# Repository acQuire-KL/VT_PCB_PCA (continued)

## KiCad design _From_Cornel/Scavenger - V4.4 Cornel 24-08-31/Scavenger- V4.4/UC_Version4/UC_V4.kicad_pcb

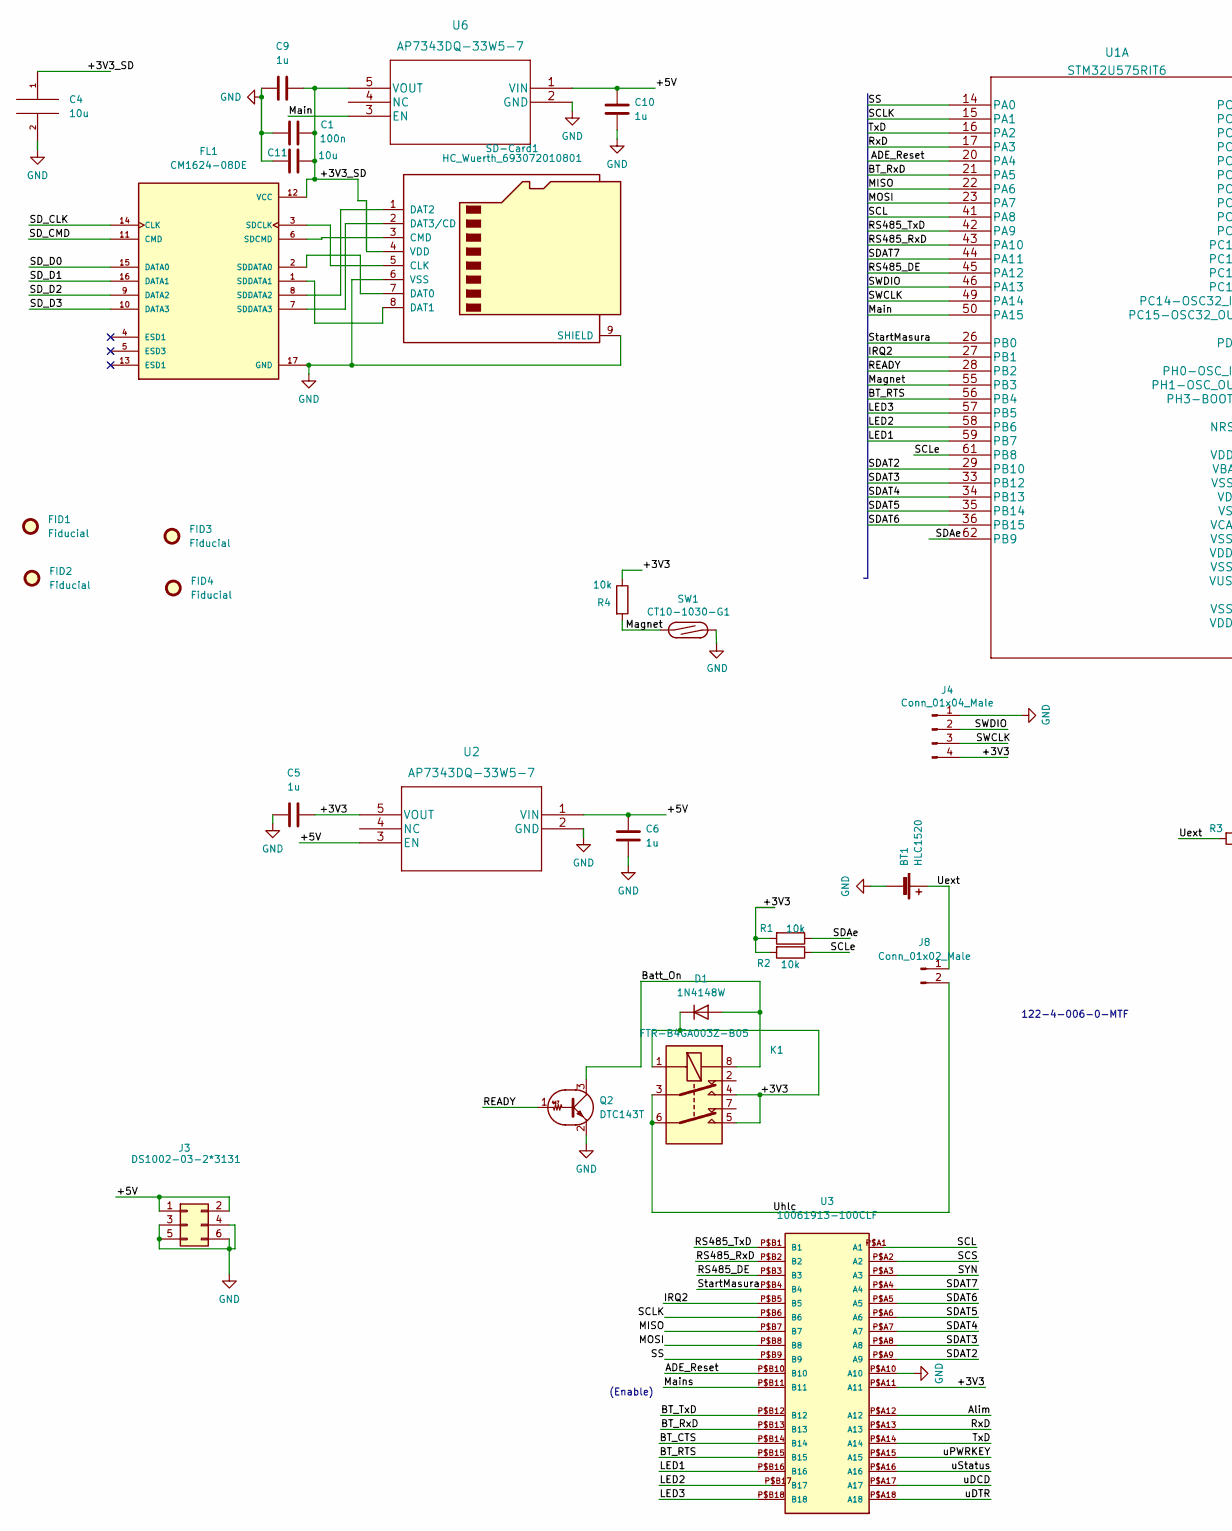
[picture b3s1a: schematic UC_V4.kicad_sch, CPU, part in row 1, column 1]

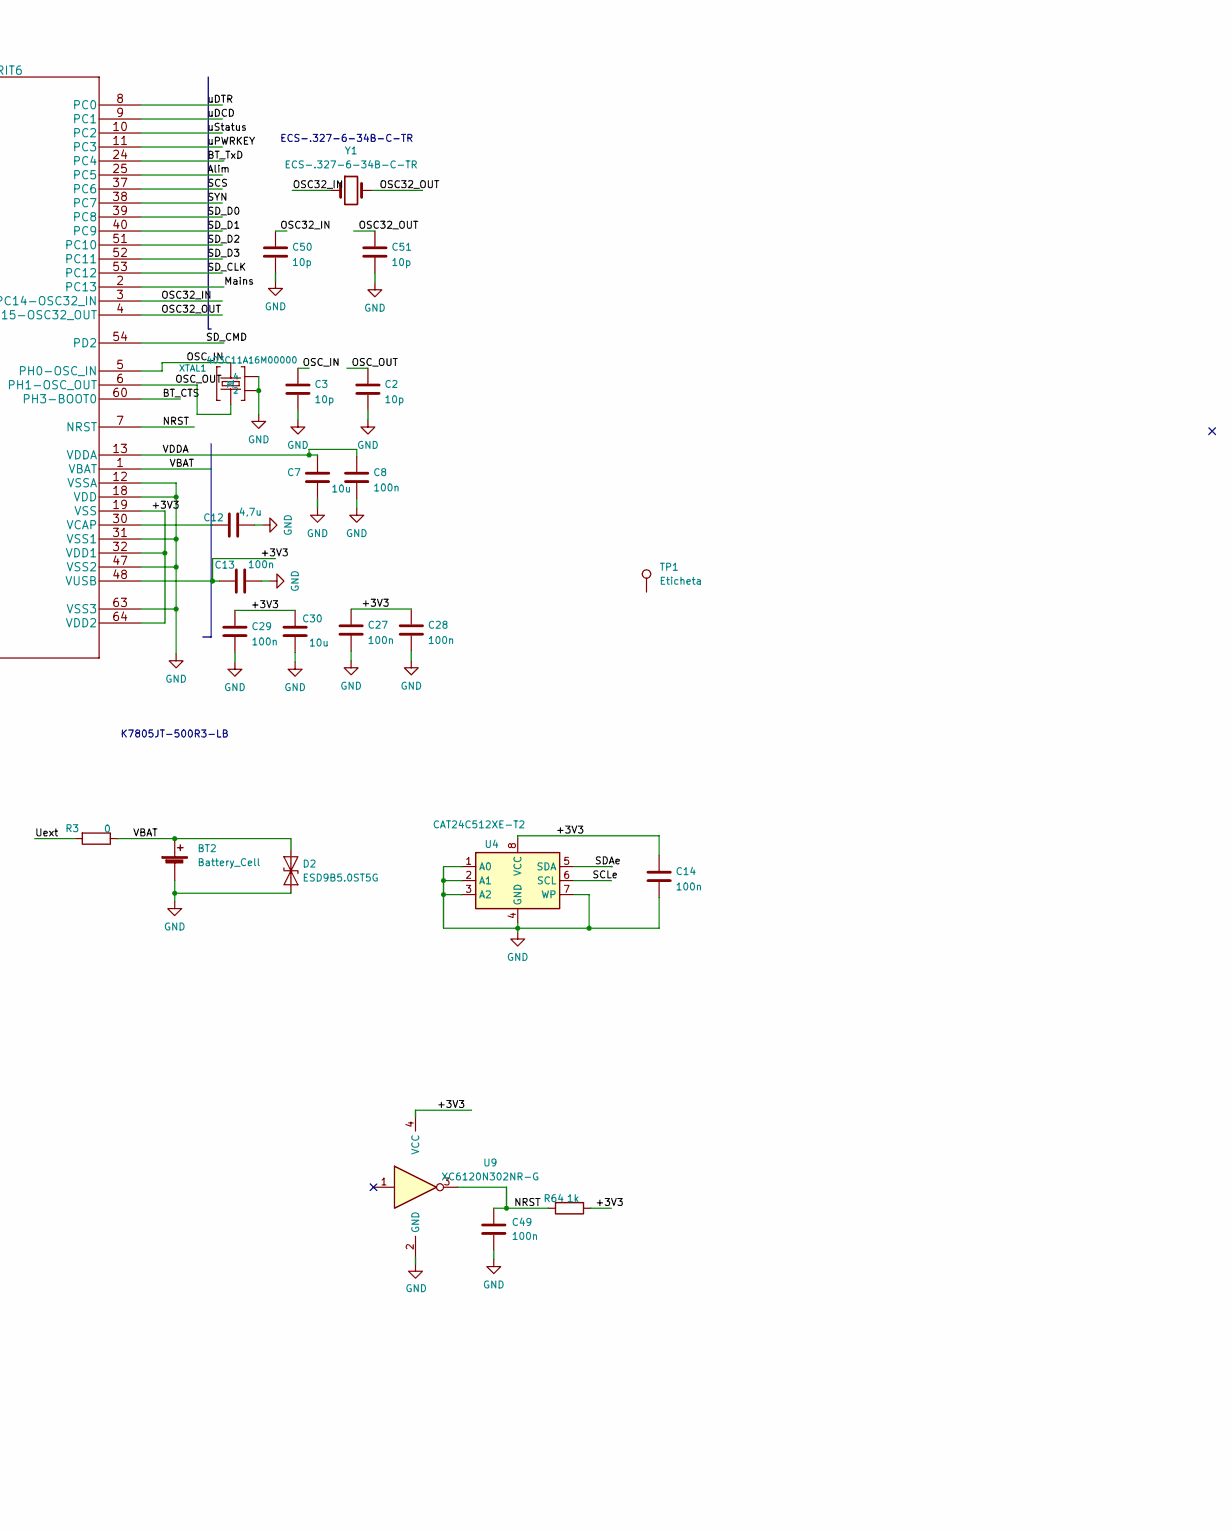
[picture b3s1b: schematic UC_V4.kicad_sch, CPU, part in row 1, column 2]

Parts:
BT1: HLC1520
BT2: Battery_Cell; BatteryHolder_Keystone_3002_1x2032
C1, C8, C13, C14, C27, C28, C29, C49: 100n; C_0603_1608Metric
C2, C3, C50, C51: 10p; C_0603_1608Metric
C4, C7, C11, C30: 10u; C_1206_3216Metric
C5, C6, C9, C10: 1u; C_0603_1608Metric
C12: 4,7u; C_1206_3216Metric
D1: 1N4148W; D_SOD-123
D2: ESD9B5.0ST5G; SOD-923_ONS
FID1, FID2, FID3, FID4: Fiducial; Fiducial_1mm_Mask2mm
FL1: CM1624-08DE; FIL_CM1624; PARTREV 4
J3: DS1002-03-2*3131; PinSocket_2x03_P2.54mm_Vertical
J4: Conn_01x04_Male; PinHeader_1x04_P2.54mm_Vertical
J8: Conn_01x02_Male; PinHeader_1x02_P2.54mm_Vertical
K1: FTR-B4GA003Z-B05; Relay_Fujitsu_FTR-B4GA003
Q2: DTC143T; SOT-23
R1, R2, R4: 10k; R_0603_1608Metric
R3: 0; R_0603_1608Metric
R64: 1k; R_0603_1608Metric
SD-Card1: HC_Wuerth_693072010801; microSD_HC_Wuerth_693072010801
SW1: CT10-1030-G1; SW_SPST_REED_CT10-XXXX-G1
TP1: Eticheta
U1: STM32U575RIT6; LQFP-64_10x10mm_P0.5mm
U2, U6: AP7343DQ-33W5-7; AP3012KTR-G1
U3: 10061913-100CLF; MPN 10061913-100CLF
U4: CAT24C512XE-T2; SO-8_3.9x4.9mm_P1.27mm
U9: XC6120N302NR-G; SC-82AA
XTAL1: 403C11A16M00000; Crystal_SMD_SeikoEpson_TSX3225-4Pin_3.2x2.5mm
Y1: ECS-.327-6-34B-C-TR; Crystal_SMD_EuroQuartz_EQ161-2Pin_3.2x1.5mm

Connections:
/+3V3: C5.2, C13.1, C14.1, C27.1, C28.1, C29.1, C30.1, D1.1 (K), J4.4, K1.1, K1.4, K1.5, R1.2, R2.2, R4.1, R64.1, U1.19 (VSS), U1.32 (VDD1), U1.48 (VUSB), U1.64 (VDD2), U2.5 (VOUT), U3.P$A11 (A11), U4.8 (VCC), U9.4 (VCC)
/+3V3_SD: C1.2, C4.1, C9.2, C11.2, FL1.12 (VCC), SD-Card1.4 (VDD), U6.5 (VOUT)
/+5V: C6.1, C10.1, J3.1, J3.2, U2.1 (VIN), U2.3 (EN), U6.1 (VIN)
/ADE_Reset: U1.20 (PA4), U3.P$B10 (B10)
/Alim: U1.25 (PC5), U3.P$A12 (A12)
/BT_CTS: U1.60 (PH3-BOOT0), U3.P$B14 (B14)
/BT_RTS: U1.56 (PB4), U3.P$B15 (B15)
/BT_RxD: U1.21 (PA5), U3.P$B13 (B13)
/BT_TxD: U1.24 (PC4), U3.P$B12 (B12)
/Batt_On: D1.2 (A), K1.8, Q2.3 (C)
/IRQ2: U1.27 (PB1), U3.P$B5 (B5)
/LED1: U1.59 (PB7), U3.P$B16 (B16)
/LED2: U1.58 (PB6), U3.P$B17 (B17)
/LED3: U1.57 (PB5), U3.P$B18 (B18)
/MISO: U1.22 (PA6), U3.P$B7 (B7)
/MOSI: U1.23 (PA7), U3.P$B8 (B8)
/Magnet: R4.2, SW1.1, U1.55 (PB3)
/Main: U1.50 (PA15), U6.3 (EN)
/Mains: U1.2 (PC13), U3.P$B11 (B11)
/NRST: C49.1, R64.2, U1.7 (NRST), U9.3
/OSC32_IN: C50.1, U1.3 (PC14-OSC32_IN), Y1.1
/OSC32_OUT: C51.1, U1.4 (PC15-OSC32_OUT), Y1.2
/OSC_IN: C3.1, U1.5 (PH0-OSC_IN), XTAL1.3
/OSC_OUT: C2.1, U1.6 (PH1-OSC_OUT), XTAL1.1
/READY: Q2.1 (B), U1.28 (PB2)
/RS485_DE: U1.45 (PA12), U3.P$B3 (B3)
/RS485_RxD: U1.43 (PA10), U3.P$B2 (B2)
/RS485_TxD: U1.42 (PA9), U3.P$B1 (B1)
/RxD: U1.17 (PA3), U3.P$A13 (A13)
/SCL: U1.41 (PA8), U3.P$A1 (A1)
/SCLK: U1.15 (PA1), U3.P$B6 (B6)
/SCLe: R2.1, U1.61 (PB8), U4.6 (SCL)
/SCS: U1.37 (PC6), U3.P$A2 (A2)
/SDAT2: U1.29 (PB10), U3.P$A9 (A9)
/SDAT3: U1.33 (PB12), U3.P$A8 (A8)
/SDAT4: U1.34 (PB13), U3.P$A7 (A7)
/SDAT5: U1.35 (PB14), U3.P$A6 (A6)
/SDAT6: U1.36 (PB15), U3.P$A5 (A5)
/SDAT7: U1.44 (PA11), U3.P$A4 (A4)
/SDAe: R1.1, U1.62 (PB9), U4.5 (SDA)
/SD_CLK: FL1.14 (CLK), U1.53 (PC12)
/SD_CMD: FL1.11 (CMD), U1.54 (PD2)
/SD_D0: FL1.15 (DATA0), U1.39 (PC8)
/SD_D1: FL1.16 (DATA1), U1.40 (PC9)
/SD_D2: FL1.9 (DATA2), U1.51 (PC10)
/SD_D3: FL1.10 (DATA3), U1.52 (PC11)
/SS: U1.14 (PA0), U3.P$B9 (B9)
/SWCLK: J4.3, U1.49 (PA14)
/SWDIO: J4.2, U1.46 (PA13)
/SYN: U1.38 (PC7), U3.P$A3 (A3)
/StartMasura: U1.26 (PB0), U3.P$B4 (B4)
/TxD: U1.16 (PA2), U3.P$A14 (A14)
/Uext: BT1.1 (+), J8.1, R3.2
/Uhlc: J8.2, K1.3, K1.6
/VBAT: BT2.1 (+), D2.2 (A2), R3.1, U1.1 (VBAT)
/VDDA: C7.1, C8.1, U1.13 (VDDA)
/uDCD: U1.9 (PC1), U3.P$A17 (A17)
/uDTR: U1.8 (PC0), U3.P$A18 (A18)
/uPWRKEY: U1.11 (PC3), U3.P$A15 (A15)
/uStatus: U1.10 (PC2), U3.P$A16 (A16)
GND: BT1.2 (-), BT2.2 (-), C1.1, C2.2, C3.2, C4.2, C5.1, C6.2, C7.2, C8.2, C9.1, C10.2, C11.1, C12.2, C13.2, C14.2, C27.2, C28.2, C29.2, C30.2, C49.2, C50.2, C51.2, D2.1 (A1), FL1.17 (GND), J3.3, J3.4, J3.5, J3.6, J4.1, Q2.2 (E), SD-Card1.6 (VSS), SD-Card1.9 (SHIELD), SW1.2, U1.12 (VSSA), U1.18 (VDD), U1.31 (VSS1), U1.47 (VSS2), U1.63 (VSS3), U2.2 (GND), U3.P$A10 (A10), U4.1 (A0), U4.2 (A1), U4.3 (A2), U4.4 (GND), U4.7 (WP), U6.2 (GND), U9.2 (GND), XTAL1.2, XTAL1.4
unnamed: C12.1, U1.30 (VCAP)
unnamed: FL1.1 (SDDATA1), SD-Card1.8 (DAT1)
unnamed: FL1.2 (SDDATA0), SD-Card1.7 (DAT0)
unnamed: FL1.3 (SDCLK), SD-Card1.5 (CLK)
unnamed: FL1.6 (SDCMD), SD-Card1.3 (CMD)
unnamed: FL1.7 (SDDATA3), SD-Card1.2 (DAT3/CD)
unnamed: FL1.8 (SDDATA2), SD-Card1.1 (DAT2)

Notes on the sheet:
ECS-.327-6-34B-C-TR
K7805JT-500R3-LB
(Enable)
122-4-006-0-MTF

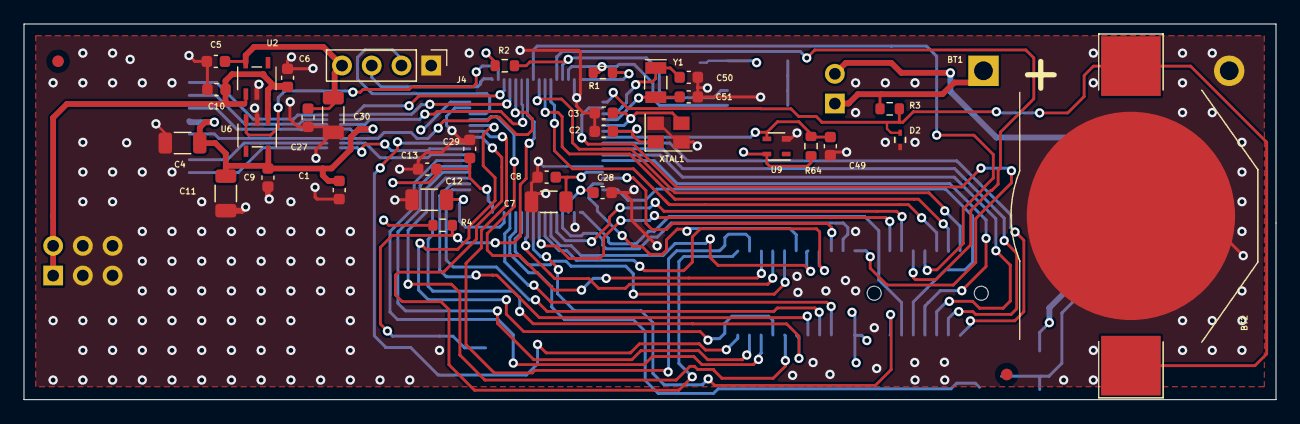
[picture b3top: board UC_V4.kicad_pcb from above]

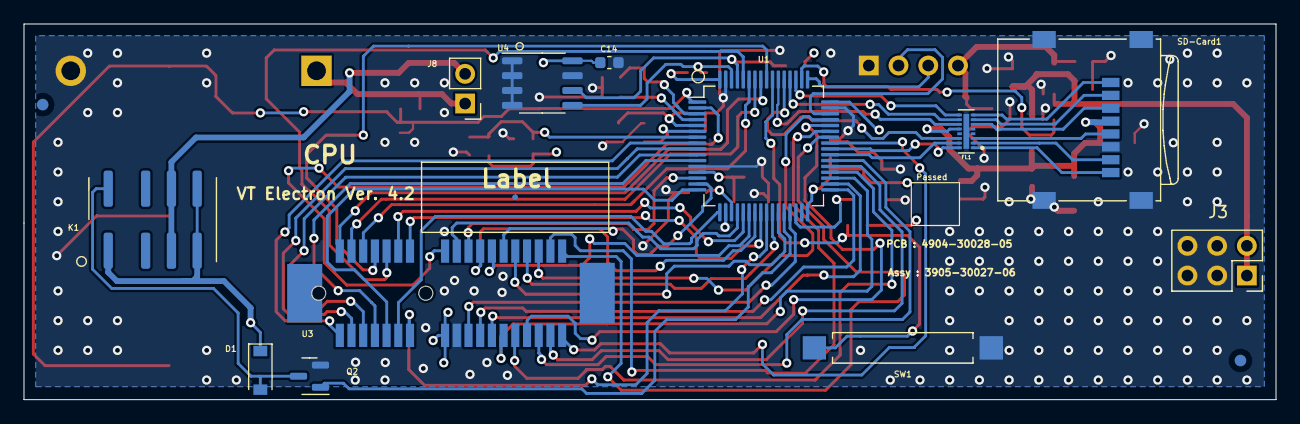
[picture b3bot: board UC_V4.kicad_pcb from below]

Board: 4 copper layers, 107.0 x 32.1 mm, 51 parts (14 on the bottom side), 68 nets.

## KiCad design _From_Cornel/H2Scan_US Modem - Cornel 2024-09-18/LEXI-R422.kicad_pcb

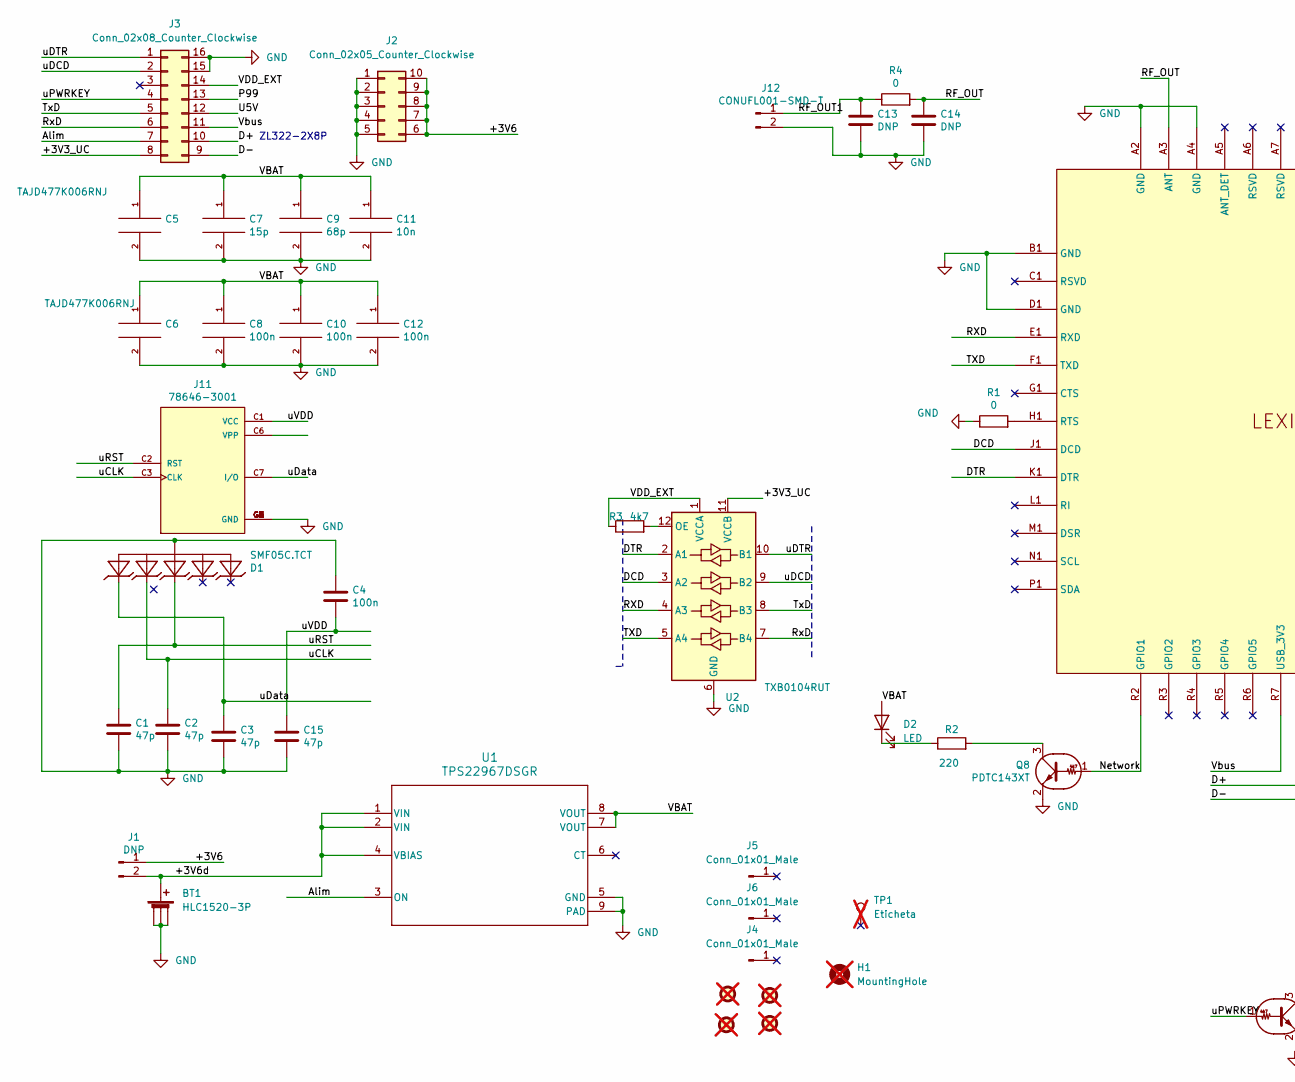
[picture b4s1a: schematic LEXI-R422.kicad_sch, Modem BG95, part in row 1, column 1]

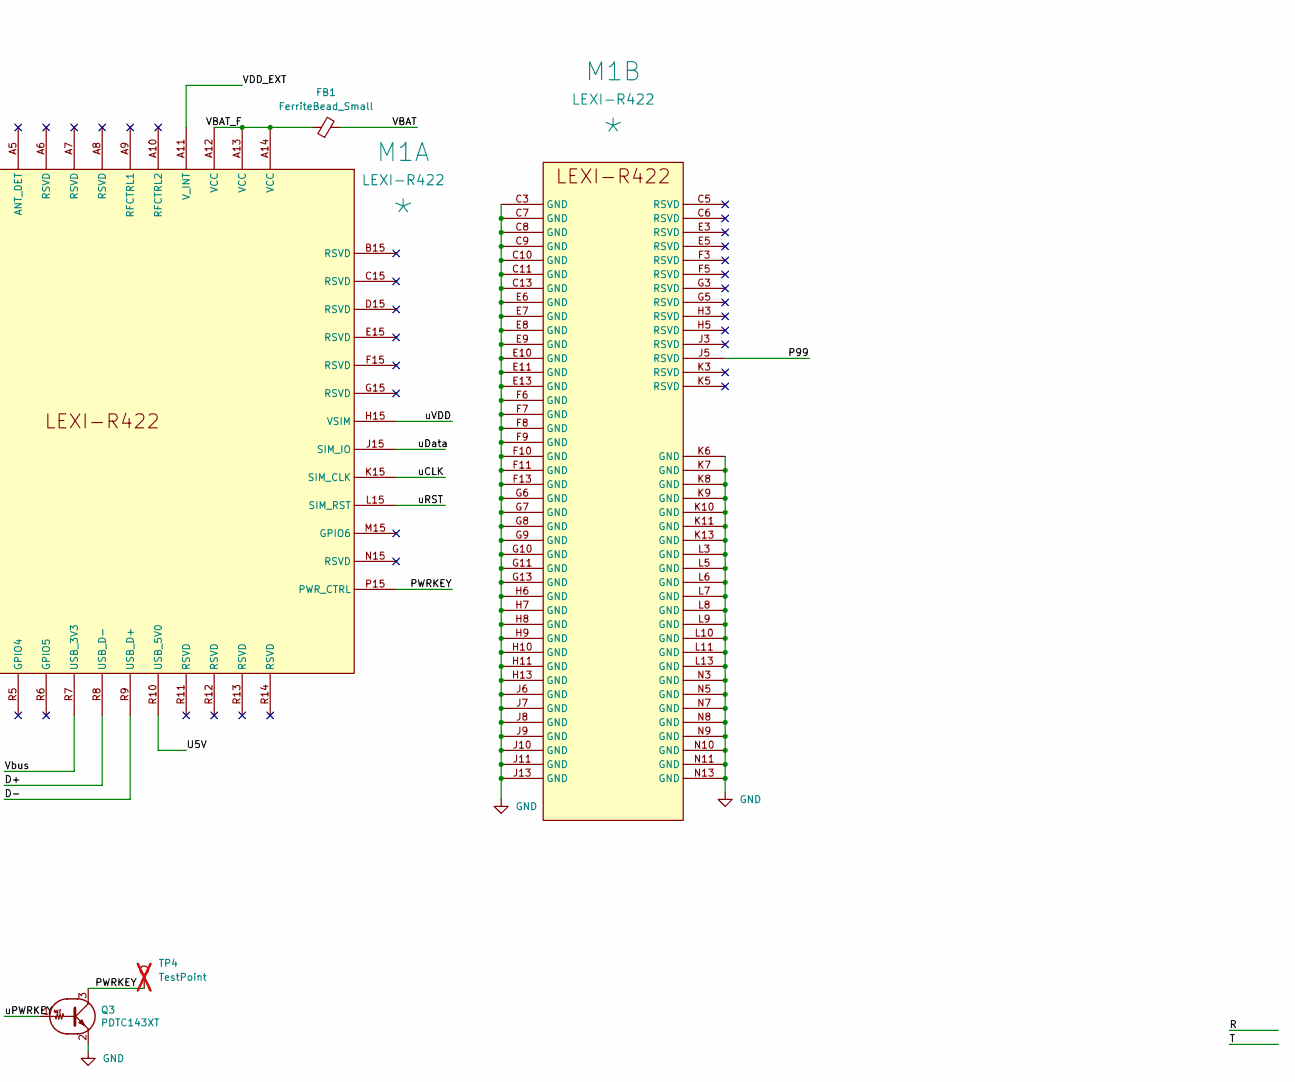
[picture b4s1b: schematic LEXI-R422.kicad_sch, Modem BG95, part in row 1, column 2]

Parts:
BT1: HLC1520-3P
C1, C2, C3, C15: 47p; C_0603_1608Metric
C4, C8, C10, C12: 100n; C_0603_1608Metric
C5, C6: TAJD477K006RNJ; CP_EIA-7361-38_AVX-V_Pad2.18x3.30mm_HandSolder
C7: 15p; C_0603_1608Metric
C9: 68p; C_0603_1608Metric
C11: 10n; C_0603_1608Metric
C13, C14: DNP; C_0603_1608Metric
D1: SMF05C.TCT; SC70-6
D2: LED; LED_0805_2012Metric
FB1: FerriteBead_Small; L_Walsin_WLFM201209x
FID1, FID2, FID3, FID4: Fiducial; Fiducial_1mm_Mask2mm; not fitted
H1: MountingHole; MountingHole_2.5mm Simpla; not fitted
J1: DNP; PinHeader_1x02_P2.54mm_Vertical_MOD
J2: Conn_02x05_Counter_Clockwise; PinHeader_2x05_P2.54mm_Vertical_SMD_MOD
J3: Conn_02x08_Counter_Clockwise; PinHeader_2x08_P2.54mm_Vertical_SMD_MOD
J4, J5, J6: Conn_01x01_Male; TestPoint_Pad_5.1x5.1mm
J11: 78646-3001; MOLEX_78646-3001; DIGI-KEY_PART_NUMBER WM9364CT-ND
J12: CONUFL001-SMD-T; U.FL_Molex_MCRF_73412-0110_Vertical
M1: LEXI-R422; LEXI; Manufacturer P/N *
Q3, Q8: PDTC143XT; SOT-23
R1, R4: 0; R_0603_1608Metric
R2: 220; R_0603_1608Metric
R3: 4k7; R_0603_1608Metric
TP1: Eticheta; not fitted
TP4: TestPoint; TestPoint_Pad_D1.5mm; not fitted
U1: TPS22967DSGR; WSON-8-1EP_2x2mm_P0.5mm_EP0.9x1.6mm_ThermalVias
U2: TXB0104RUT; Texas_R_PUQFN-N12

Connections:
/+3V3_UC: J3.8, U2.11 (VCCB)
/+3V6: J1.1, J2.6, J2.7, J2.8, J2.9, J2.10
/+3V6d: BT1.1 (+), J1.2, U1.1 (VIN), U1.2 (VIN), U1.4 (VBIAS)
/Alim: J3.7, U1.3 (ON)
/D+: J3.10, M1.R8 (USB_D-)
/D-: J3.9, M1.R9 (USB_D+)
/DCD: M1.J1 (DCD), U2.3 (A2)
/DTR: M1.K1 (DTR), U2.2 (A1)
/Network: M1.R2 (GPIO1), Q8.1 (B)
/P99: J3.13, M1.J5 (RSVD)
/PWRKEY: M1.P15 (PWR_CTRL), Q3.3 (C), TP4.1
/RF_OUT: C14.1, M1.A3 (ANT), R4.2
/RF_OUT1: C13.1, J12.1, R4.1
/RXD: M1.E1 (RXD), U2.4 (A3)
/RxD: J3.6, U2.7 (B4)
/TXD: M1.F1 (TXD), U2.5 (A4)
/TxD: J3.5, U2.8 (B3)
/U5V: J3.12, M1.R10 (USB_5V0)
/VBAT: C5.1, C6.1, C7.1, C8.1, C9.1, C10.1, C11.1, C12.1, D2.2 (A), FB1.2, U1.7 (VOUT), U1.8 (VOUT)
/VBAT_F: FB1.1, M1.A12 (VCC), M1.A13 (VCC), M1.A14 (VCC)
/VDD_EXT: J3.14, M1.A11 (V_INT), R3.1, U2.1 (VCCA)
/Vbus: J3.11, M1.R7 (USB_3V3)
/uCLK: C2.1, D1.5, J11.C3 (CLK), M1.K15 (SIM_CLK)
/uDCD: J3.2, U2.9 (B2)
/uDTR: J3.1, U2.10 (B1)
/uData: C3.1, D1.6, J11.C7 (I/O), M1.J15 (SIM_IO)
/uPWRKEY: J3.4, Q3.1 (B)
/uRST: C1.1, D1.4, J11.C2 (RST), M1.L15 (SIM_RST)
/uVDD: C4.2, C15.1, J11.C1 (VCC), M1.H15 (VSIM)
GND: BT1.2 (-), BT1.3 (-), BT1.4 (-), C1.2, C2.2, C3.2, C4.1, C5.2, C6.2, C7.2, C8.2, C9.2, C10.2, C11.2, C12.2, C13.2, C14.2, C15.2, D1.2, J2.1, J2.2, J2.3, J2.4, J2.5, J3.15, J3.16, J11.C5 (GND), J11.G1 (GND), J11.G2 (GND), J11.G3 (GND), J11.G4 (GND), J11.G5 (GND), J11.G6 (GND), J12.2, M1.A2 (GND), M1.A4 (GND), M1.B1 (GND), M1.C3 (GND), M1.C7 (GND), M1.C8 (GND), M1.C9 (GND), M1.C10 (GND), M1.C11 (GND), M1.C13 (GND), M1.D1 (GND), M1.E6 (GND), M1.E7 (GND), M1.E8 (GND), M1.E9 (GND), M1.E10 (GND), M1.E11 (GND), M1.E13 (GND), M1.F6 (GND), M1.F7 (GND), M1.F8 (GND), M1.F9 (GND), M1.F10 (GND), M1.F11 (GND), M1.F13 (GND), M1.G6 (GND), M1.G7 (GND), M1.G8 (GND), M1.G9 (GND), M1.G10 (GND), M1.G11 (GND), M1.G13 (GND), M1.H6 (GND), M1.H7 (GND), M1.H8 (GND), M1.H9 (GND), M1.H10 (GND), M1.H11 (GND), M1.H13 (GND), M1.J6 (GND), M1.J7 (GND), M1.J8 (GND), M1.J9 (GND), M1.J10 (GND), M1.J11 (GND), M1.J13 (GND), M1.K6 (GND), M1.K7 (GND), M1.K8 (GND), M1.K9 (GND), M1.K10 (GND), M1.K11 (GND), M1.K13 (GND), M1.L3 (GND), M1.L5 (GND), M1.L6 (GND), M1.L7 (GND), M1.L8 (GND), M1.L9 (GND), M1.L10 (GND), M1.L11 (GND), M1.L13 (GND), M1.N3 (GND), M1.N5 (GND), M1.N7 (GND), M1.N8 (GND), M1.N9 (GND), M1.N10 (GND), M1.N11 (GND), M1.N13 (GND), Q3.2 (E), Q8.2 (E), R1.1, U1.5 (GND), U1.9 (PAD), U2.6 (GND)
unnamed: D2.1 (K), R2.1
unnamed: M1.H1 (RTS), R1.2
unnamed: Q8.3 (C), R2.2
unnamed: R3.2, U2.12 (OE)

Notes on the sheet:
ZL322-2X8P

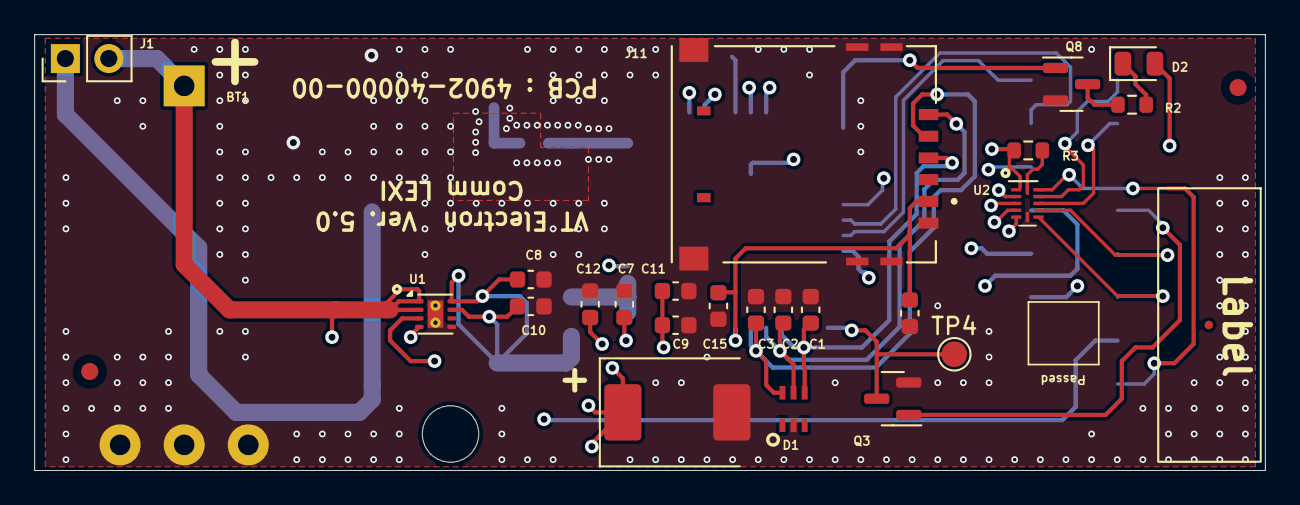
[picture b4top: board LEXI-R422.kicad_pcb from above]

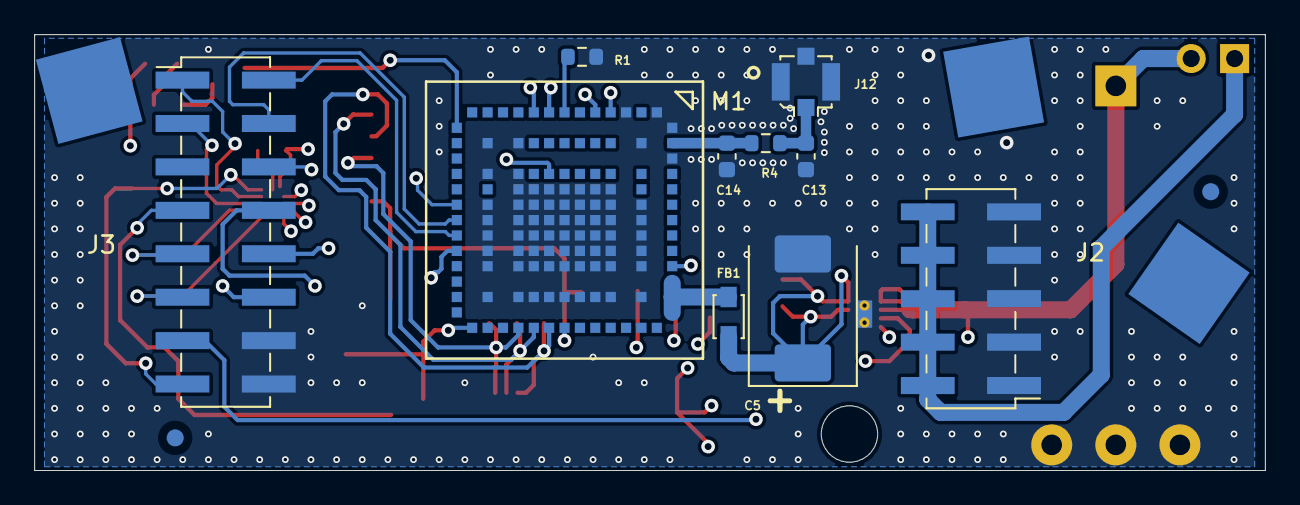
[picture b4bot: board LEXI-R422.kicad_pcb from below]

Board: 4 copper layers, 72.0 x 25.5 mm, 43 parts (15 on the bottom side), 34 nets.

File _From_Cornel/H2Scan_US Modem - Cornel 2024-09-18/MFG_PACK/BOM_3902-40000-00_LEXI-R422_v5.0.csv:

"VTPN","Reference","Value","Datasheet","Footprint","Qty","DNP"
"4200-00010-00","BT1","HLC1520-3P","~","Battery:HLC1520-3P","1",""
"4106-00080-00","C1,C2,C3,C15","47p","~","Capacitor_SMD:C_0603_1608Metric","4",""
"4106-00020-00","C4,C8,C10,C12","100n","~","Capacitor_SMD:C_0603_1608Metric","4",""
"4128-00100-00","C5,C6","TAJD477K006RNJ","~","Capacitor_Tantalum_SMD:CP_EIA-7361-38_AVX-V_Pad2.18x3.30mm_HandSolder","2",""
"4106-00070-00","C7","15p","~","Capacitor_SMD:C_0603_1608Metric","1",""
"4106-00060-00","C9","68p","~","Capacitor_SMD:C_0603_1608Metric","1",""
"4106-00015-00","C11","10n","~","Capacitor_SMD:C_0603_1608Metric","1",""
"-- mixed values --","C13,C14,J1","DNP","~","-- mixed values --","3",""
"4724-00010-00","D1","SMF05C.TCT","","Diode_SMD:SC70-6","1",""
"","FID1,FID2,FID3,FID4","Fiducial","~","Fiducial:Fiducial_1mm_Mask2mm","4","DNP"
"","H1","MountingHole","~","MountingHole:MountingHole_2.5mm  Simpla","1","DNP"
"4402-00020-00","J2","Conn_02x05_Counter_Clockwise","~","Connector_PinHeader_2.54mm:PinHeader_2x05_P2.54mm_Vertical_SMD_MOD","1",""
"4402-00030-00","J3","Conn_02x08_Counter_Clockwise","~","Connector_PinHeader_2.54mm:PinHeader_2x08_P2.54mm_Vertical_SMD_MOD","1",""
"4753-00010-00","J4,J5,J6","Conn_01x01_Male","~","TestPoint:TestPoint_Pad_5.1x5.1mm","3",""
"4414-00020-00","J11","78646-3001","","Connector_Molex:MOLEX_78646-3001","1",""
"4416-00010-00","J12","CONUFL001-SMD-T","~","Connector_Coaxial:U.FL_Molex_MCRF_73412-0110_Vertical","1",""
"4500-00010-00","Q3,Q8","PDTC143XT","","Package_TO_SOT_SMD:SOT-23","2",""
"4006-00001-00","R1,R4","0","~","Resistor_SMD:R_0603_1608Metric","2",""
"4006-00020-00","R2","220","~","Resistor_SMD:R_0603_1608Metric","1",""
"4006-00150-00","R3","4k7","~","Resistor_SMD:R_0603_1608Metric","1",""
"","TP1","Eticheta","~","Symbol:Eticheta","1","DNP"
"4702-01010-00","U1","TPS22967DSGR","TPS22967DSGR","Package_SON:WSON-8-1EP_2x2mm_P0.5mm_EP0.9x1.6mm_ThermalVias","1",""
"4702-00010-00","U2","TXB0104RUT","http://www.ti.com/lit/ds/symlink/txb0104.pdf","Package_DFN_QFN:Texas_R_PUQFN-N12","1",""
"4300-01010-00","FB1","FerriteBead_Small","~","Inductor_SMD:L_Walsin_WLFM201209x","1",""
"4752-01010-00","D2","LED","~","LED_SMD:LED_0805_2012Metric","1",""
"","TP4","TestPoint","~","TestPoint:TestPoint_Pad_D1.5mm","1","DNP"
"4716-00020-00","M1","LEXI-R422","","ublox:LEXI","1",""

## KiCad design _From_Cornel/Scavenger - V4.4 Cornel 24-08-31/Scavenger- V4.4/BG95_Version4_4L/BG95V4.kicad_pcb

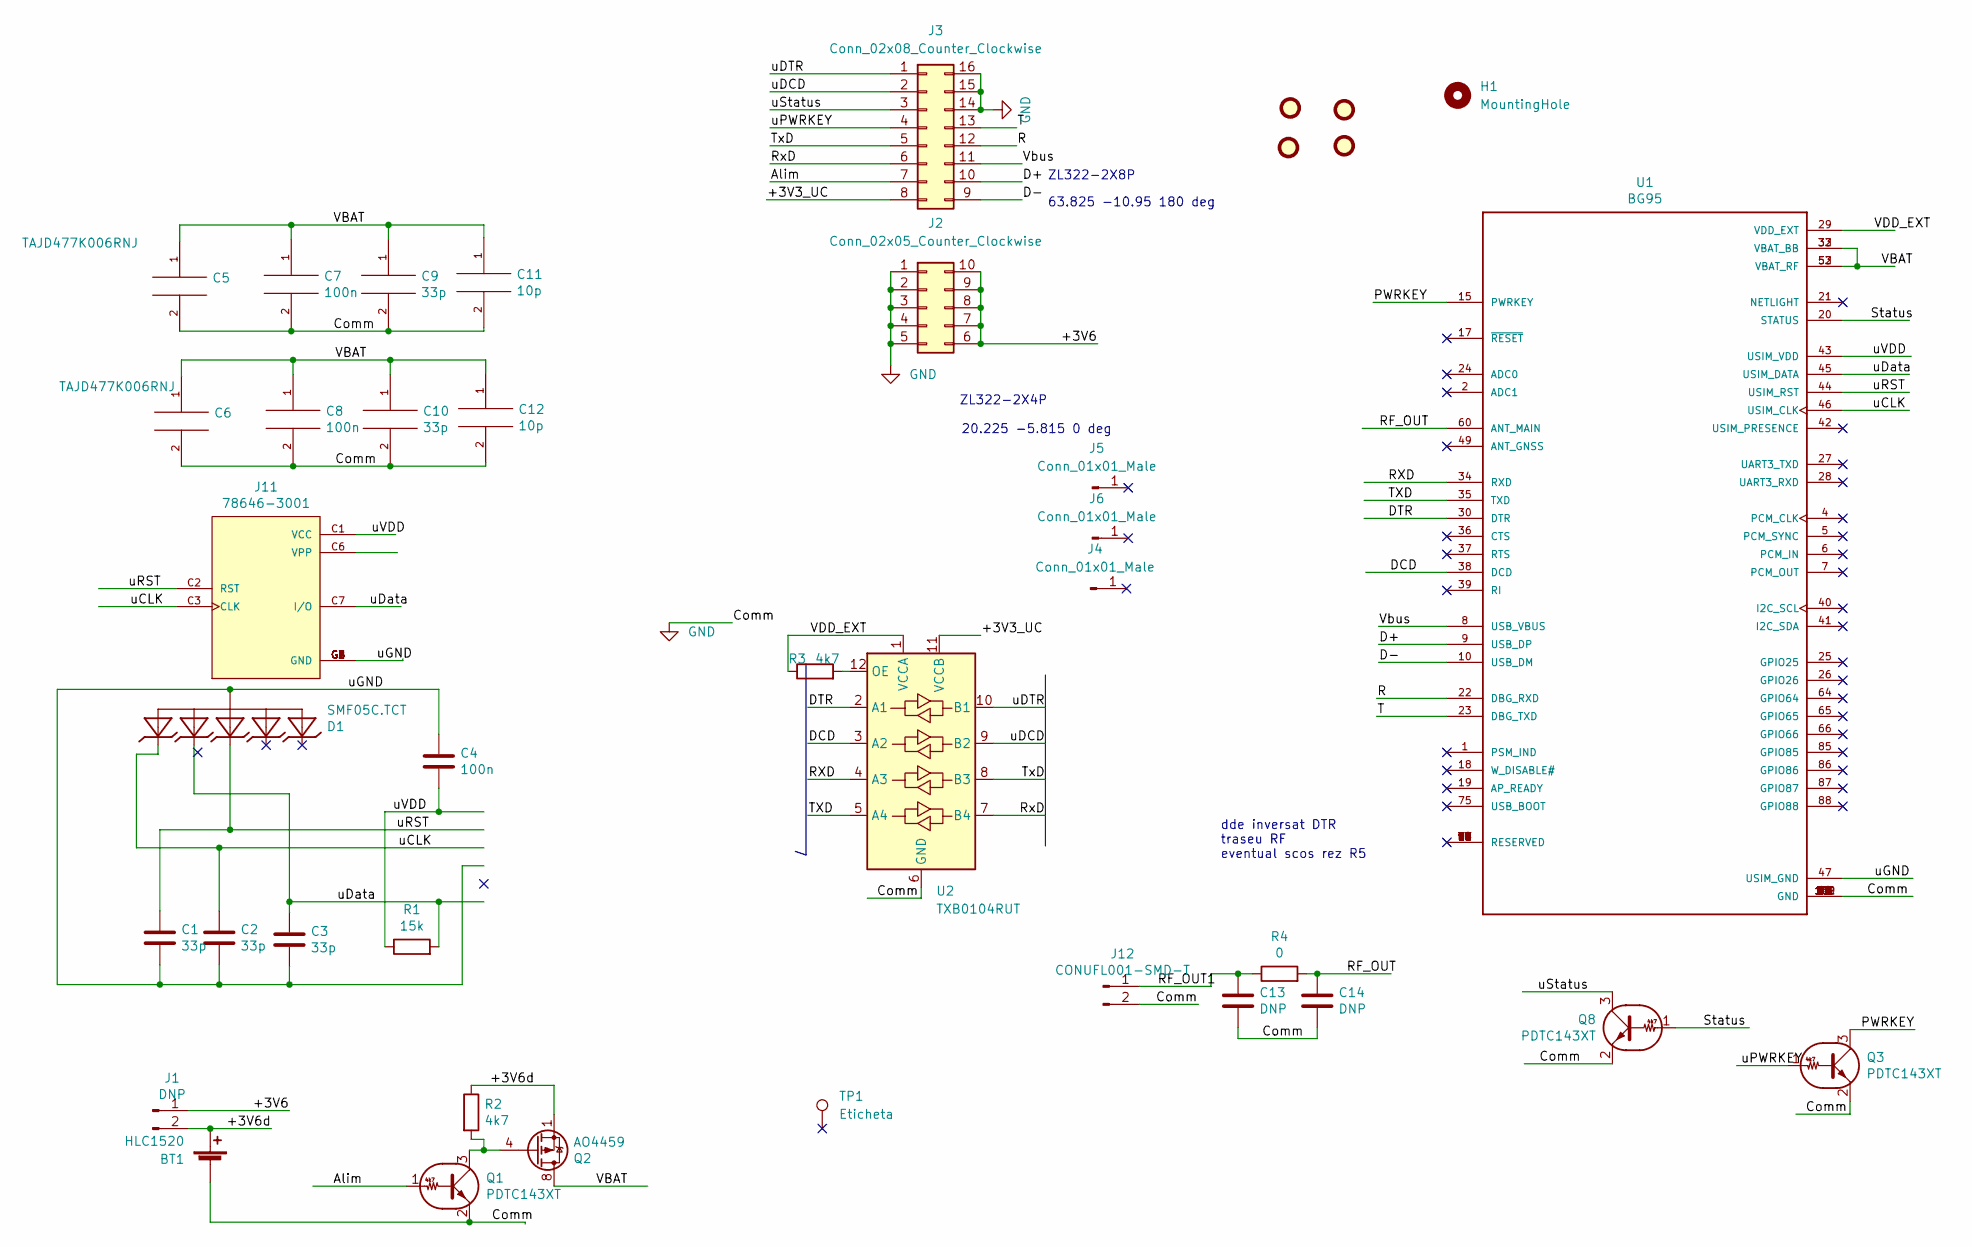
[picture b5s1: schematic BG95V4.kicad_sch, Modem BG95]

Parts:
BT1: HLC1520
C1, C2, C3: 33p; C_0603_1608Metric
C4: 100n; C_0603_1608Metric
C5, C6: TAJD477K006RNJ; CP_EIA-7361-38_AVX-V_Pad2.18x3.30mm_HandSolder
C7, C8: 100n; C_0603_1608Metric_Pad1.05x0.95mm_HandSolder
C9, C10: 33p; C_0603_1608Metric_Pad1.05x0.95mm_HandSolder
C11, C12: 10p; C_0603_1608Metric_Pad1.05x0.95mm_HandSolder
C13, C14: DNP; C_0603_1608Metric
D1: SMF05C.TCT; SC70-6
FID1, FID2, FID3, FID4: Fiducial; Fiducial_1mm_Mask2mm
H1: MountingHole; MountingHole_2.5mm Simpla
J1: DNP; PinHeader_1x02_P2.54mm_Vertical
J2: Conn_02x05_Counter_Clockwise; PinHeader_2x05_P2.54mm_Vertical_SMD_MOD
J3: Conn_02x08_Counter_Clockwise; PinHeader_2x08_P2.54mm_Vertical_SMD_MOD
J4, J5, J6: Conn_01x01_Male; TestPoint_Pad_5.1x5.1mm
J11: 78646-3001; MOLEX_78646-3001; DIGI-KEY_PART_NUMBER WM9364CT-ND
J12: CONUFL001-SMD-T; U.FL_Molex_MCRF_73412-0110_Vertical
Q1, Q3, Q8: PDTC143XT; SOT-23
Q2: AO4459; SOIC-8_3.9x4.9mm_P1.27mm
R1: 15k; R_0603_1608Metric
R2, R3: 4k7; R_0603_1608Metric
R4: 0; R_0603_1608Metric
TP1: Eticheta
U1: BG95; XCVR_BG95M3LA-64-SGNS
U2: TXB0104RUT; Texas_R_PUQFN-N12

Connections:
/+3V3_UC: J3.8, U2.11 (VCCB)
/+3V6: J1.1, J2.6, J2.7, J2.8, J2.9, J2.10
/+3V6d: BT1.1 (+), J1.2, Q2.1 (S), Q2.2 (S), Q2.3 (S), R2.1
/Alim: J3.7, Q1.1 (B)
/D+: J3.10, U1.9 (USB_DP)
/D-: J3.9, U1.10 (USB_DM)
/DCD: U1.38 (DCD), U2.3 (A2)
/DTR: U1.30 (DTR), U2.2 (A1)
/PWRKEY: Q3.3 (C), U1.15 (PWRKEY)
/R: J3.12, U1.22 (DBG_RXD)
/RF_OUT: C14.1, R4.2, U1.60 (ANT_MAIN)
/RF_OUT1: C13.1, J12.1, R4.1
/RXD: U1.34 (RXD), U2.4 (A3)
/RxD: J3.6, U2.7 (B4)
/Status: Q8.1 (B), U1.20 (STATUS)
/T: J3.13, U1.23 (DBG_TXD)
/TXD: U1.35 (TXD), U2.5 (A4)
/TxD: J3.5, U2.8 (B3)
/VBAT: C5.1, C6.1, C7.1, C8.1, C9.1, C10.1, C11.1, C12.1, Q2.5 (D), Q2.6 (D), Q2.7 (D), Q2.8 (D), U1.32 (VBAT_BB), U1.33 (VBAT_BB), U1.52 (VBAT_RF), U1.53 (VBAT_RF)
/VDD_EXT: R3.1, U1.29 (VDD_EXT), U2.1 (VCCA)
/Vbus: J3.11, U1.8 (USB_VBUS)
/uCLK: C2.1, D1.6, J11.C3 (CLK), U1.46 (USIM_CLK)
/uDCD: J3.2, U2.9 (B2)
/uDTR: J3.1, U2.10 (B1)
/uData: C3.1, D1.5, J11.C7 (I/O), R1.2, U1.45 (USIM_DATA)
/uGND: C1.2, C2.2, C3.2, C4.1, D1.2, J11.C5 (GND), J11.G1 (GND), J11.G2 (GND), J11.G3 (GND), J11.G4 (GND), J11.G5 (GND), J11.G6 (GND), U1.47 (USIM_GND)
/uPWRKEY: J3.4, Q3.1 (B)
/uRST: C1.1, D1.4, J11.C2 (RST), U1.44 (USIM_RST)
/uStatus: J3.3, Q8.3 (C)
/uVDD: C4.2, J11.C1 (VCC), R1.1, U1.43 (USIM_VDD)
GND: BT1.2 (-), C5.2, C6.2, C7.2, C8.2, C9.2, C10.2, C11.2, C12.2, C13.2, C14.2, J2.1, J2.2, J2.3, J2.4, J2.5, J3.14, J3.15, J3.16, J12.2, Q1.2 (E), Q3.2 (E), Q8.2 (E), U1.3 (GND), U1.31 (GND), U1.48 (GND), U1.50 (GND), U1.54 (GND), U1.55 (GND), U1.58 (GND), U1.59 (GND), U1.61 (GND), U1.62 (GND), U1.67 (GND), U1.68 (GND), U1.69 (GND), U1.70 (GND), U1.71 (GND), U1.72 (GND), U1.73 (GND), U1.74 (GND), U1.79 (GND), U1.80 (GND), U1.81 (GND), U1.82 (GND), U1.89 (GND), U1.90 (GND), U1.91 (GND), U1.100 (GND), U1.101 (GND), U1.102 (GND), U2.6 (GND)
unnamed: Q1.3 (C), Q2.4 (G), R2.2
unnamed: R3.2, U2.12 (OE)

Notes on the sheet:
ZL322-2X8P
20.225 -5.815 0 deg
dde inversat DTR traseu RF eventual scos rez R5
ZL322-2X4P
63.825 -10.95 180 deg

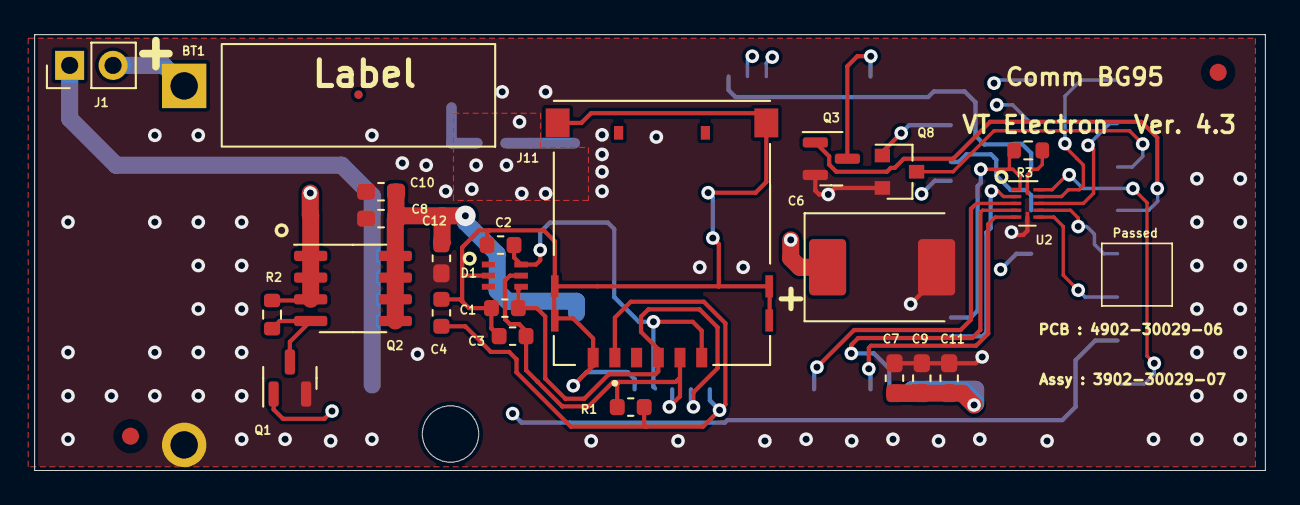
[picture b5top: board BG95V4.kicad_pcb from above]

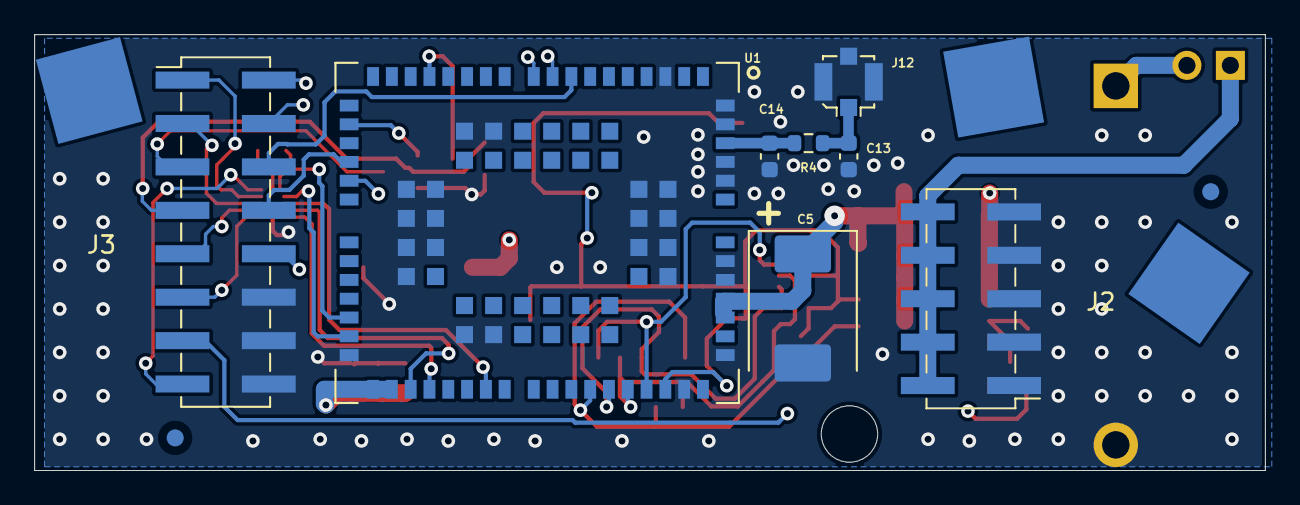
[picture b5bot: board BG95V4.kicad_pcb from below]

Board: 4 copper layers, 72.0 x 25.5 mm, 40 parts (13 on the bottom side), 33 nets.

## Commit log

2025-04-03 ADE filess upload
2025-04-03 ADE-Aux filess upload
2025-04-03 BG95 filess upload
2025-04-03 Lexi filess upload
2025-04-03 Main filess upload
2025-04-03 Main_H2Scan filess upload
2025-04-03 MFG_PACKs (zip)Sent to ECAS filess upload
2025-04-03 Shield Protction filess upload
2025-04-03 UC filess upload
2025-04-03 Original Files from Cornell via email upload
